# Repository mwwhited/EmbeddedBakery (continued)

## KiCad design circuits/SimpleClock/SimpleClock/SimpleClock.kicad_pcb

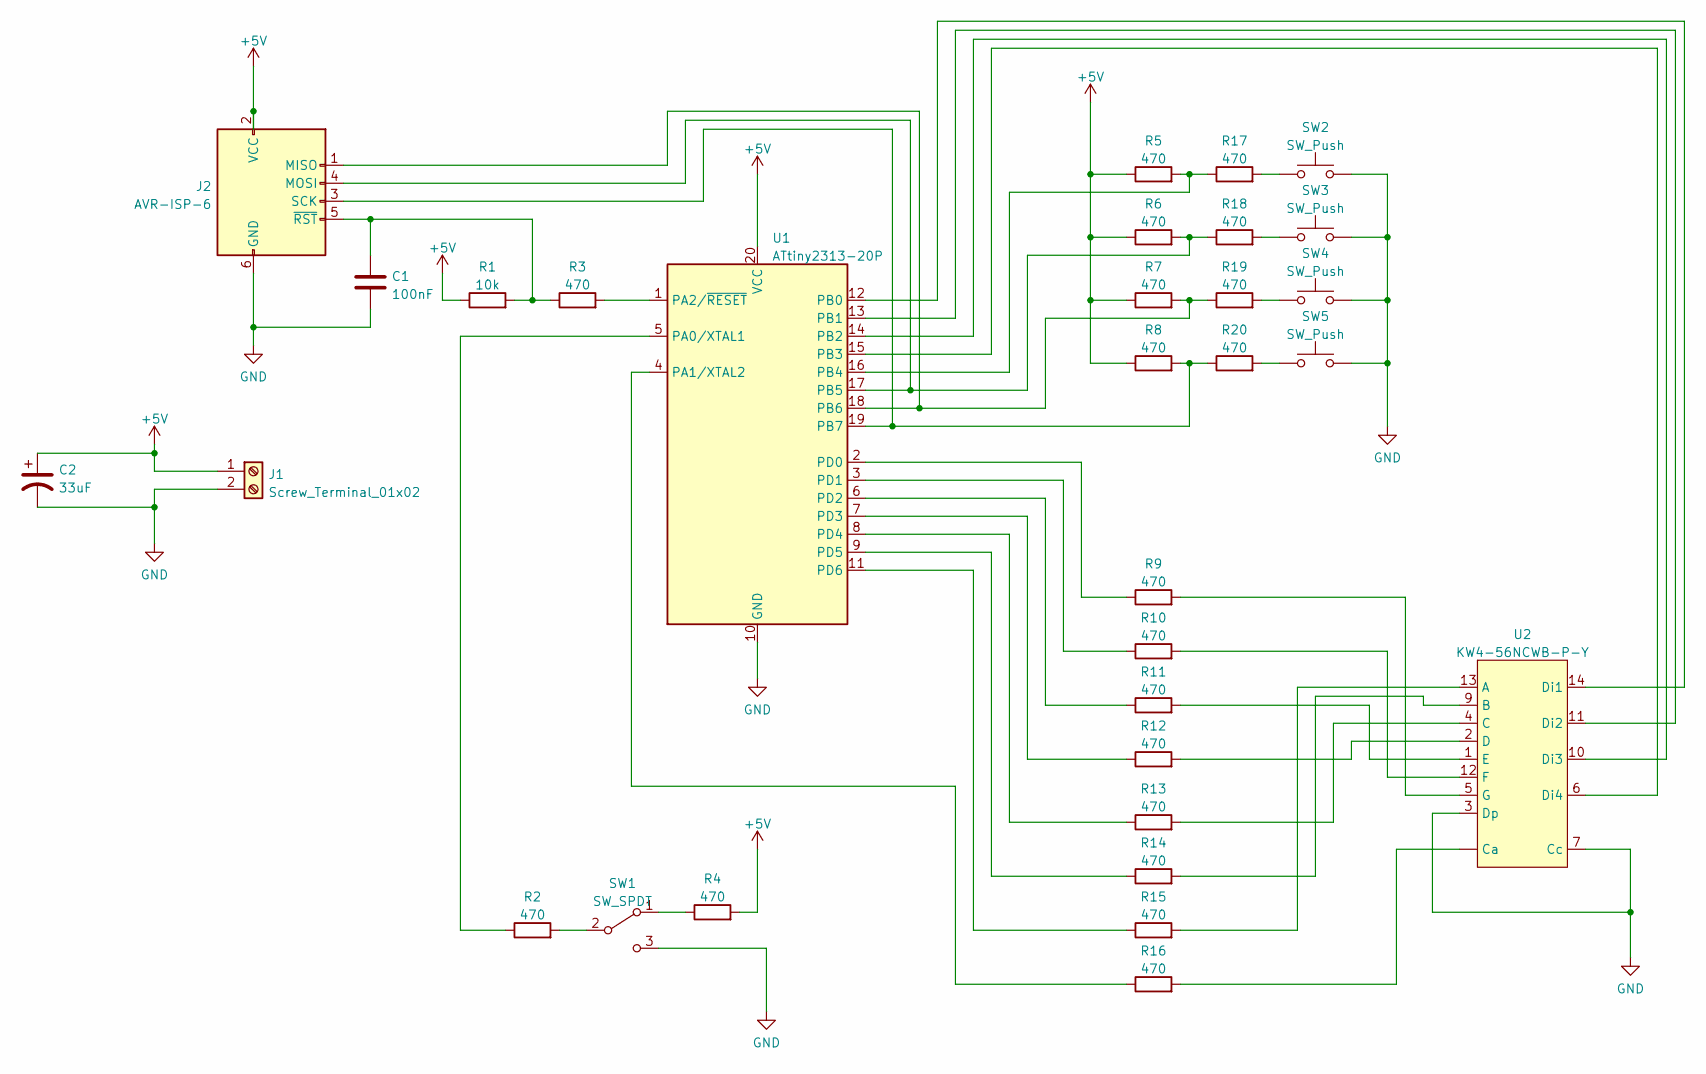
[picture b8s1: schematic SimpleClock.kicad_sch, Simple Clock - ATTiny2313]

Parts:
C1: 100nF; C_Disc_D3.0mm_W2.0mm_P2.50mm
C2: 33uF; CP_Radial_D4.0mm_P2.00mm
J1: Screw_Terminal_01x02; TerminalBlock_Altech_AK300-2_P5.00mm
J2: AVR-ISP-6; PinHeader_2x03_P2.54mm_Vertical
R1: 10k; R_Axial_DIN0207_L6.3mm_D2.5mm_P10.16mm_Horizontal
R2, R3, R4, R5, R6, R7, R8, R9, R10, R11, R12, R13, R14, R15, R16, R17, R18, R19, R20: 470; R_Axial_DIN0207_L6.3mm_D2.5mm_P10.16mm_Horizontal
SW1: SW_SPDT; PinHeader_1x03_P2.54mm_Vertical
SW2, SW3, SW4, SW5: SW_Push; SW_Tactile_Straight_KSA0Axx1LFTR
U1: ATtiny2313-20P; DIP-20_W7.62mm
U2: KW4-56NCWB-P-Y; 4 Digit 7 Segment Display

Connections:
+5V: C2.1, J1.1, J2.2 (VCC), R1.1, R4.2, R5.1, R6.1, R7.1, R8.1, U1.20 (VCC)
GND: C1.2, C2.2, J1.2, J2.6 (GND), SW1.3 (C), SW2.2, SW3.2, SW4.2, SW5.2, U1.10 (GND), U2.3 (Dp), U2.7 (Cc)
unnamed: J2.1 (MISO), R7.2, R19.1, U1.18 (PB6)
unnamed: J2.3 (SCK), R8.2, R20.1, U1.19 (PB7)
unnamed: J2.4 (MOSI), R6.2, R18.1, U1.17 (PB5)
unnamed: C1.1, J2.5 (~RST), R1.2, R3.1
unnamed: R2.1, U1.5 (PA0/XTAL1)
unnamed: R2.2, SW1.2 (B)
unnamed: R3.2, U1.1 (PA2/~RESET)
unnamed: R4.1, SW1.1 (A)
unnamed: R9.1, U1.2 (PD0)
unnamed: R9.2, U2.5 (G)
unnamed: R10.1, U1.3 (PD1)
unnamed: R10.2, U2.12 (F)
unnamed: R11.1, U1.6 (PD2)
unnamed: R11.2, U2.1 (E)
unnamed: R12.1, U1.7 (PD3)
unnamed: R12.2, U2.2 (D)
unnamed: R13.1, U1.8 (PD4)
unnamed: R13.2, U2.4 (C)
unnamed: R14.1, U1.9 (PD5)
unnamed: R14.2, U2.9 (B)
unnamed: R15.1, U1.11 (PD6)
unnamed: R15.2, U2.13 (A)
unnamed: R16.1, U1.4 (PA1/XTAL2)
unnamed: R16.2, U2. (Ca)
unnamed: R5.2, R17.1, U1.16 (PB4)
unnamed: R17.2, SW2.1
unnamed: R18.2, SW3.1
unnamed: R19.2, SW4.1
unnamed: R20.2, SW5.1
unnamed: U1.12 (PB0), U2.14 (Di1)
unnamed: U1.13 (PB1), U2.11 (Di2)
unnamed: U1.14 (PB2), U2.10 (Di3)
unnamed: U1.15 (PB3), U2.6 (Di4)

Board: 2 copper layers, 31 parts (0 on the bottom side), 34 nets, no tracks yet.
